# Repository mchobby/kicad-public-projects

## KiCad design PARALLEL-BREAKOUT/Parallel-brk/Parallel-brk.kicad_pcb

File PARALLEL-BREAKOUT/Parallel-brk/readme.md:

# Parallel Breakout : Port parallel to GPIO Breakout

This board expose a Raspberry-Pi alike 2x20 GPIO with 5V and 3.3V power. __Please note that Logic is 5V only__.

This GPIO will allow to connect distant customized board through a 40 IDC cable (like Pi's).

This board connects to the Parallel Port and gets its 5V power from an micro-USB connector.

The onboard 3.3V regulator produces the required 3.3V

## Status

Status: Completed

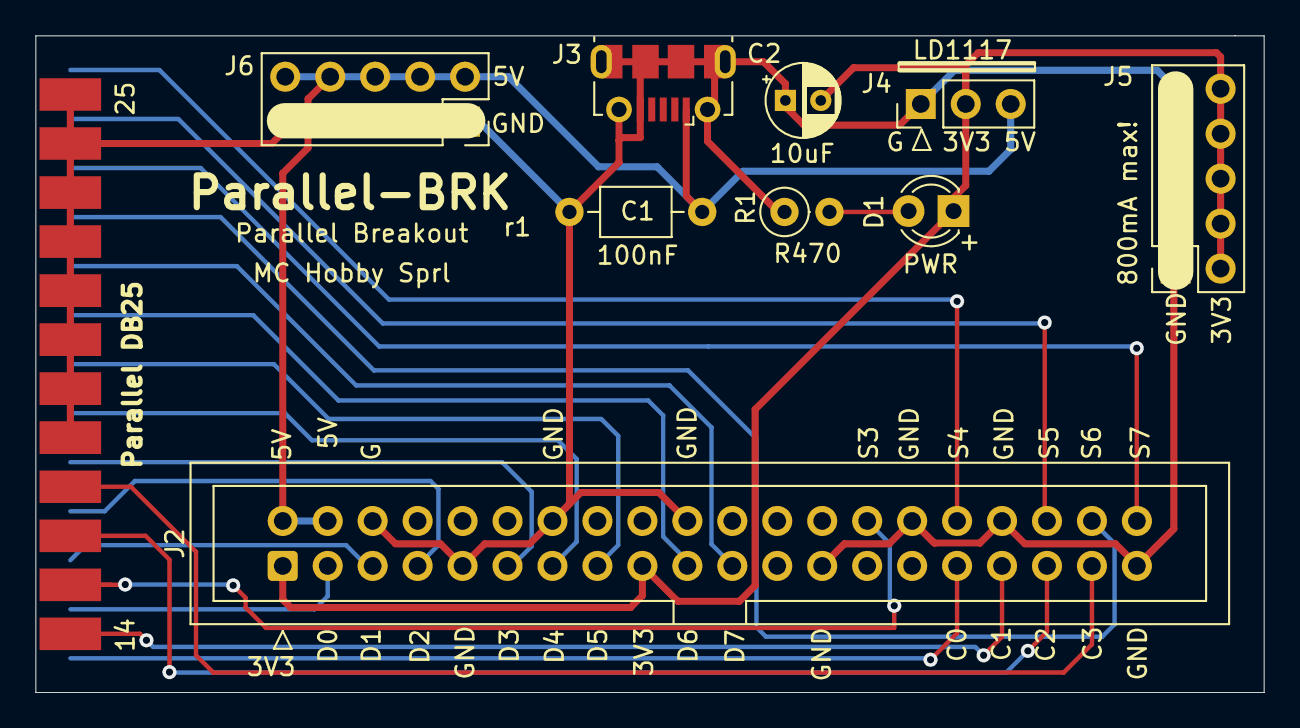
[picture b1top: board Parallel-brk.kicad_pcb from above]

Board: 2 copper layers, 69.4 x 37.1 mm, 10 parts (1 on the bottom side), 21 nets.

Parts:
C1: 100nf; C_Axial_L3.8mm_D2.6mm_P7.50mm_Horizontal
C2: 10uF; CP_Radial_D4.0mm_P2.00mm
D1: LED_PWR; LED_D3.0mm
J1: Conn_DB25; DSUB-25_Male_EdgeMount_P2.77mm
J2: Conn_RASP; IDC-Header_2x20_P2.54mm_Vertical
J3: USB_B_Micro; USB_Micro-B_Molex-105017-0001
J4: LD1117; PinHeader_1x03_P2.54mm_Vertical
J5, J6: Conn_5V; PinSocket_2x05_P2.54mm_Vertical
R1: R470; R_Axial_DIN0207_L6.3mm_D2.5mm_P2.54mm_Vertical

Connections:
+3V3: C2.2, D1.1, J2.1, J2.17, J4.2, J5.2, J5.4, J5.6, J5.8, J5.10
+5V: C1.2, J2.2, J2.4, J3.1, J4.3, J6.2, J6.4, J6.6, J6.8, J6.10
/c0: J1.1, J2.31
/c1: J1.14, J2.33
/c2: J1.16, J2.35
/c3: J1.17, J2.37
/d0: J1.2, J2.3
/d1: J1.3, J2.5
/d2: J1.4, J2.7
/d3: J1.5, J2.11
/d4: J1.6, J2.13
/d5: J1.7, J2.15
/d6: J1.8, J2.19
/d7: J1.9, J2.21
/s3: J1.15, J2.28
/s4: J1.13, J2.32
/s5: J1.12, J2.36
/s6: J1.10, J2.38
/s7: J1.11, J2.40
GND: C1.1, C2.1, J1.18, J1.19, J1.20, J1.21, J1.22, J1.23, J1.24, J1.25, J2.6, J2.9, J2.14, J2.20, J2.25, J2.30, J2.34, J2.39, J3.5, J3.6, J4.1, J5.1, J5.3, J5.5, J5.7, J5.9, J6.1, J6.3, J6.5, J6.7, J6.9, R1.1
unnamed: D1.2, R1.2

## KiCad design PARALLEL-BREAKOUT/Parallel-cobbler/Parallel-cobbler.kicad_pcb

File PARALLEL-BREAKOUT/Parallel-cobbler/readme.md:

# Parallel Cobbler : parallel GPIO to Cobbler

Make th 2x20 GPIO translated to a Cobbler.

 __Please remember that Logic level is 5V only__.

Using a Cobbler with a breadboard will make the prototyping tasks so easy.

## Status

Status: Completed

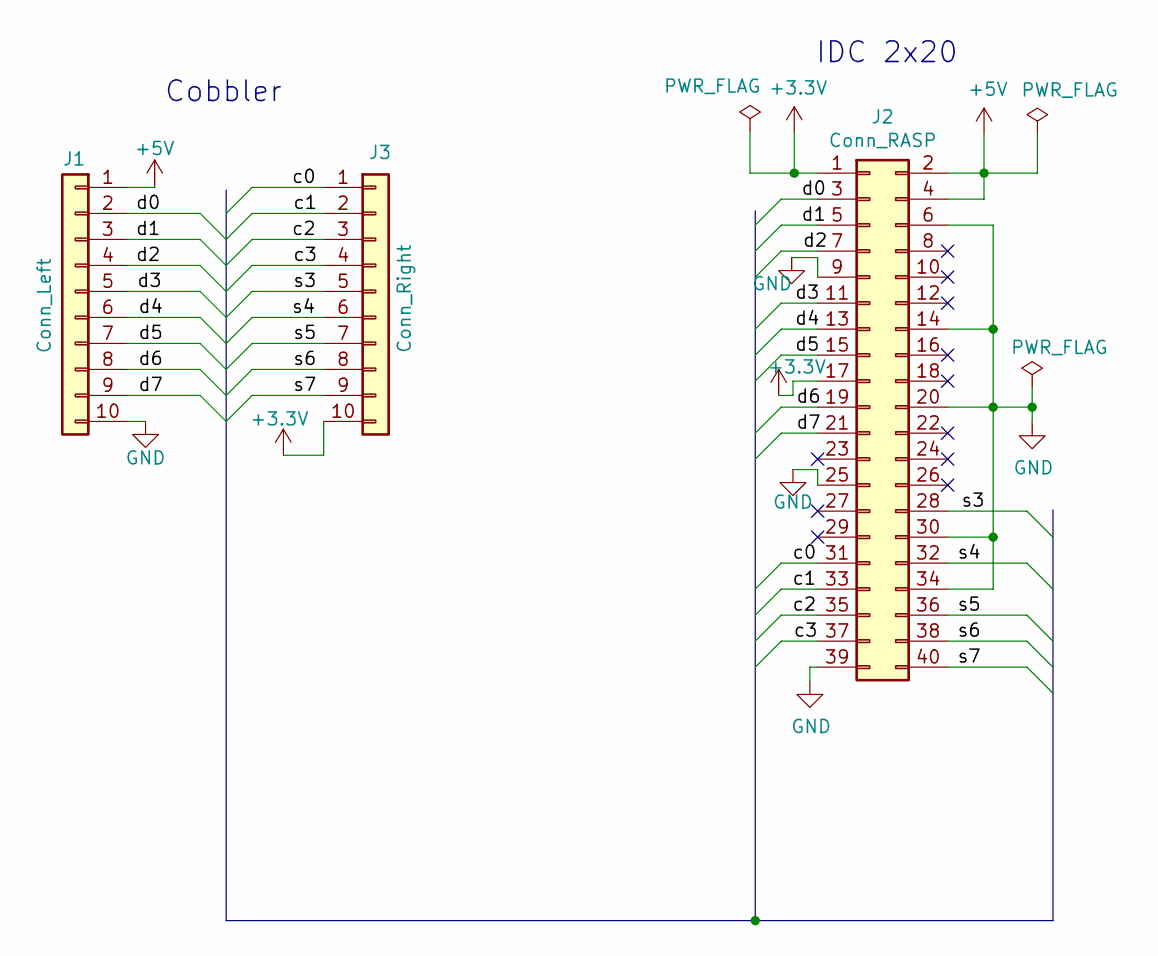
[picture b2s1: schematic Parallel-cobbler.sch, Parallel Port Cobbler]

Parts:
J1: Conn_Left; PinHeader_1x10_P2.54mm_Vertical
J2: Conn_RASP; IDC-Header_2x20_P2.54mm_Vertical
J3: Conn_Right; PinHeader_1x10_P2.54mm_Vertical

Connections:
+3V3: J2.1, J2.17, J3.10
+5V: J1.1, J2.2, J2.4
/c0: J2.31, J3.1
/c1: J2.33, J3.2
/c2: J2.35, J3.3
/c3: J2.37, J3.4
/d0: J1.2, J2.3
/d1: J1.3, J2.5
/d2: J1.4, J2.7
/d3: J1.5, J2.11
/d4: J1.6, J2.13
/d5: J1.7, J2.15
/d6: J1.8, J2.19
/d7: J1.9, J2.21
/s3: J2.28, J3.5
/s4: J2.32, J3.6
/s5: J2.36, J3.7
/s6: J2.38, J3.8
/s7: J2.40, J3.9
GND: J1.10, J2.6, J2.9, J2.14, J2.20, J2.25, J2.30, J2.34, J2.39

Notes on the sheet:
Cobbler
IDC 2x20

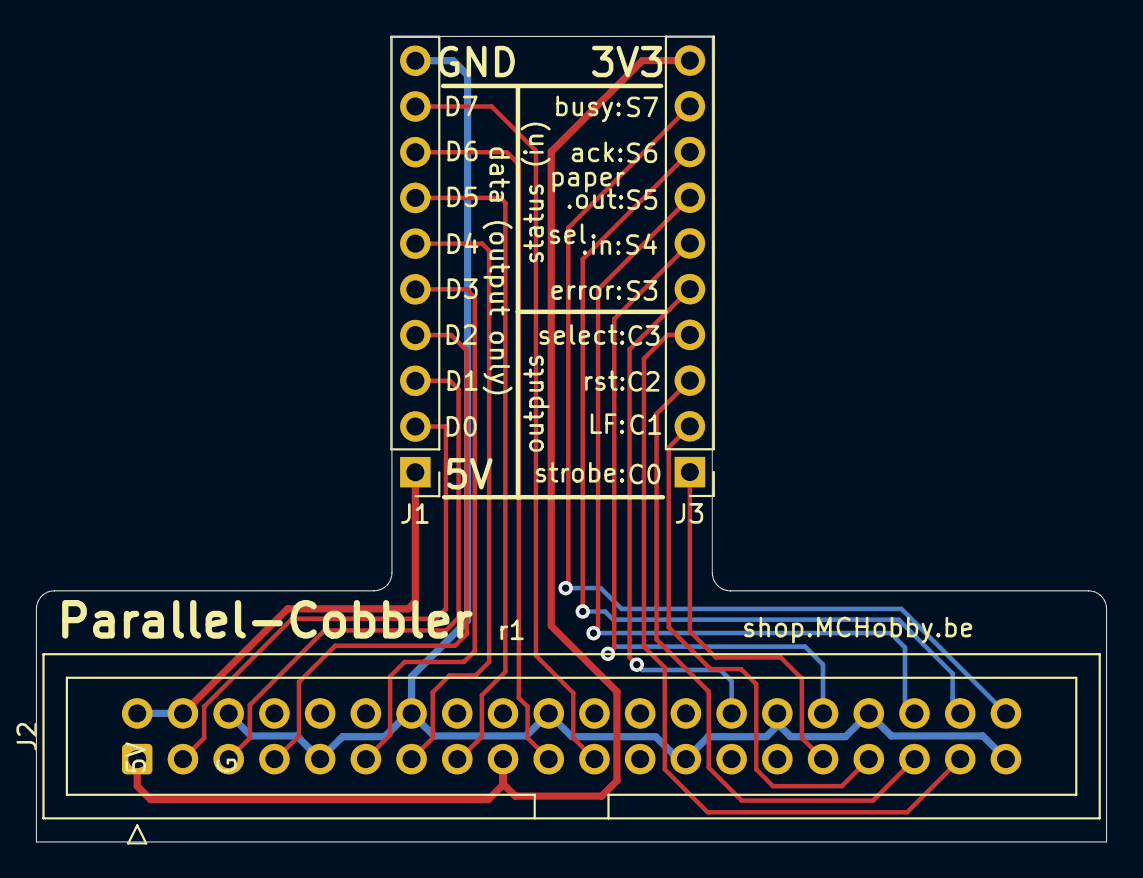
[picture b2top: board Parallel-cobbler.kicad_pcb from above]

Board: 2 copper layers, 59.5 x 44.8 mm, 3 parts (0 on the bottom side), 20 nets.

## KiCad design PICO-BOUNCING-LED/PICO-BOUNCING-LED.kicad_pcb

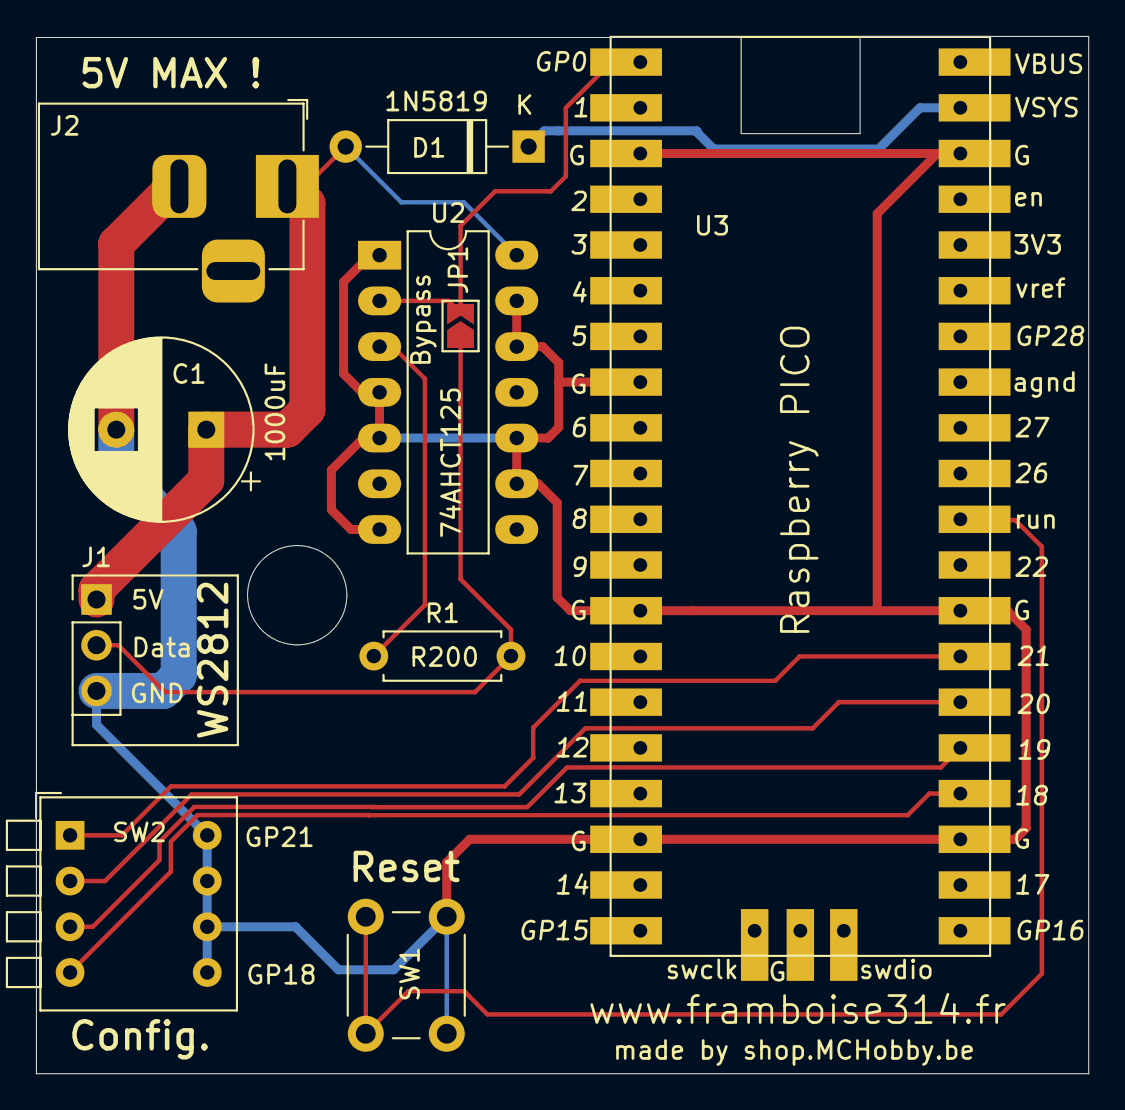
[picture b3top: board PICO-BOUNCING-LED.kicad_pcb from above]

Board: 2 copper layers, 58.5 x 57.6 mm, 10 parts (0 on the bottom side), 11 nets.

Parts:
C1: C1000uF; CP_Radial_D10.0mm_P5.00mm
D1: 1N5819; D_A-405_P10.16mm_Horizontal
J1: Conn_Pixels; PinHeader_1x03_P2.54mm_Vertical
J2: Power_Jack; BarrelJack_Horizontal
JP1: Bypass; SolderJumper-2_P1.3mm_Open_TrianglePad1.0x1.5mm
R1: R200; R_Axial_DIN0207_L6.3mm_D2.5mm_P7.62mm_Horizontal
SW1: Reset; SW_PUSH_6mm
SW2: CONFIG; SW_DIP_SPSTx04_Piano_10.8x11.72mm_W7.62mm_P2.54mm
U2: 74AHCT125; DIP-14_W7.62mm_LongPads
U3: pico; PICO

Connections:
/neopixel: JP1.2, U2.2, U3.1
GND: C1.2, J1.3, J2.2, SW1.2, SW2.5, SW2.6, SW2.7, SW2.8, U2.1, U2.4, U2.5, U2.7, U2.9, U2.10, U2.12, U2.13, U3.3, U3.8, U3.13, U3.18, U3.23, U3.28, U3.38
unnamed: C1.1, D1.2, J1.1, J2.1, U2.14
unnamed: D1.1, U3.39
unnamed: J1.2, JP1.1, R1.2
unnamed: R1.1, U2.3
unnamed: SW1.1, U3.30
unnamed: SW2.1, U3.27
unnamed: SW2.2, U3.26
unnamed: SW2.3, U3.25
unnamed: SW2.4, U3.24
